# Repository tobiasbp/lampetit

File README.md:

# Lampetit Conversion
A project to convert the Lampetit lamp by Louis Poulsen to a portable LED lamp.

# Create the Gerber files

The following is the high level view of the process. Read the
[description from JLCPVB](https://jlcpcb.com/help/article/16-How-to-generate-Gerber-and-Drill-files-in-KiCad-6)
for all the details.

1. File -> Fabrication outputs -> Gerbers
2. Press _Plot_ to greate Gerbers
3. Press _Generate Drill Files..._

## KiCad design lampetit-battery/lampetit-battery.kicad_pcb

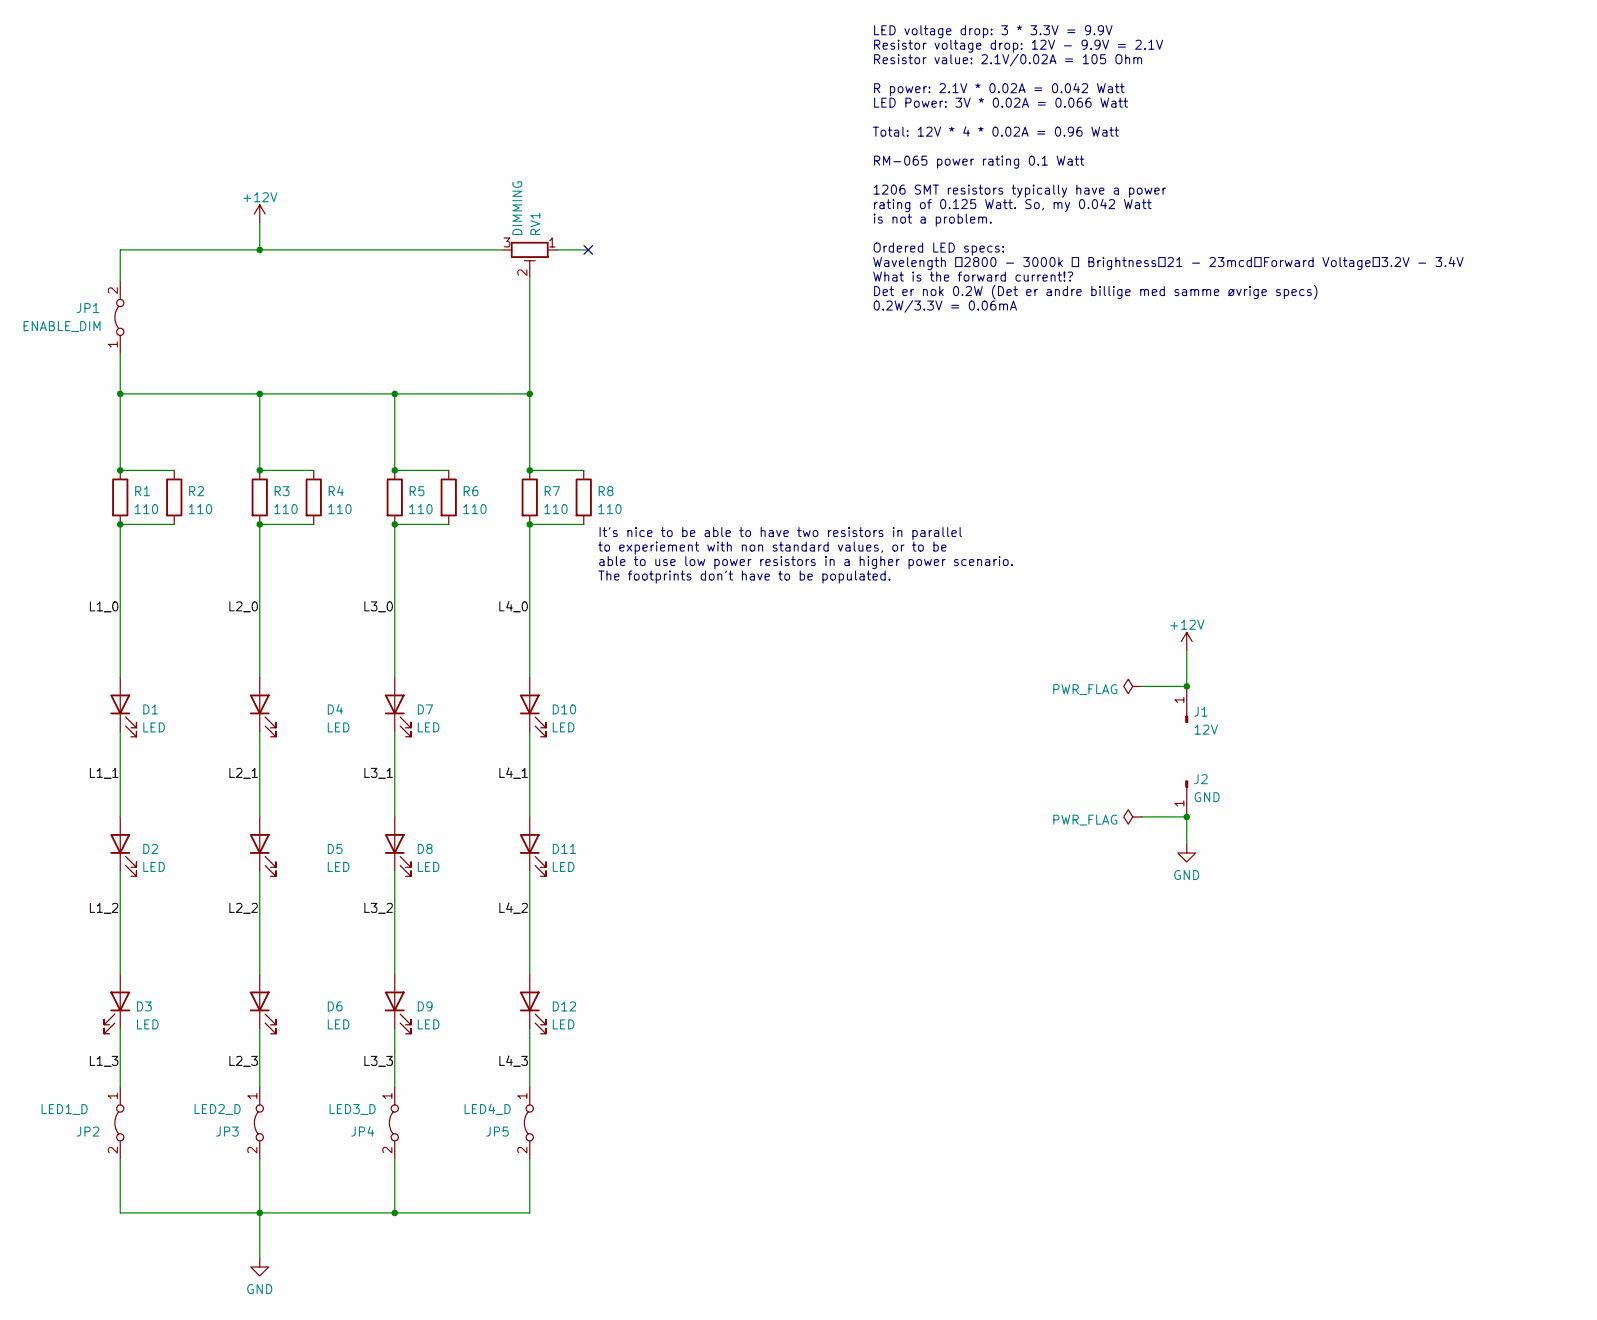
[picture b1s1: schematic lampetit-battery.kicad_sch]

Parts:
D1, D2, D3, D4, D5, D6, D7, D8, D9, D10, D11, D12: LED; LED_PLCC_2835_Handsoldering
J1: 12V; PinHeader_1x01_P2.54mm_Vertical
J2: GND; PinHeader_1x01_P2.54mm_Vertical
JP1: ENABLE_DIM; SolderJumper-2_P1.3mm_Bridged_Pad1.0x1.5mm
JP2: LED1_D; SolderJumper-2_P1.3mm_Bridged_Pad1.0x1.5mm
JP3: LED2_D; SolderJumper-2_P1.3mm_Bridged_Pad1.0x1.5mm
JP4: LED3_D; SolderJumper-2_P1.3mm_Bridged_Pad1.0x1.5mm
JP5: LED4_D; SolderJumper-2_P1.3mm_Bridged_Pad1.0x1.5mm
R1, R2, R3, R4, R5, R6, R7, R8: 110; R_1206_3216Metric_Pad1.30x1.75mm_HandSolder
RV1: DIMMING; Potentiometer_Runtron_RM-065_Vertical

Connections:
+12V: J1.1, JP1.2 (B), RV1.3
/L1_0: D1.2 (A), R1.2, R2.2
/L1_1: D1.1 (K), D2.2 (A)
/L1_2: D2.1 (K), D3.2 (A)
/L1_3: D3.1 (K), JP2.1 (A)
/L2_0: D4.2 (A), R3.2, R4.2
/L2_1: D4.1 (K), D5.2 (A)
/L2_2: D5.1 (K), D6.2 (A)
/L2_3: D6.1 (K), JP3.1 (A)
/L3_0: D7.2 (A), R5.2, R6.2
/L3_1: D7.1 (K), D8.2 (A)
/L3_2: D8.1 (K), D9.2 (A)
/L3_3: D9.1 (K), JP4.1 (A)
/L4_0: D10.2 (A), R7.2, R8.2
/L4_1: D10.1 (K), D11.2 (A)
/L4_2: D11.1 (K), D12.2 (A)
/L4_3: D12.1 (K), JP5.1 (A)
GND: J2.1, JP2.2 (B), JP3.2 (B), JP4.2 (B), JP5.2 (B)
unnamed: JP1.1 (A), R1.1, R2.1, R3.1, R4.1, R5.1, R6.1, R7.1, R8.1, RV1.2

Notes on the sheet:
LED voltage drop: 3 * 3.3V = 9.9V Resistor voltage drop: 12V - 9.9V = 2.1V Resistor value: 2.1V/0.02A = 105 Ohm R power: 2.1V * 0.02A = 0.042 Watt LED Power: 3V * 0.02A = 0.066 Watt Total: 12V * 4 * 0.02A = 0.96 Watt RM-065 power rating 0.1 Watt 1206 SMT resistors typically have a power rating of 0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
It's nice to be able to have two resistors in parallel to experiement with non standard values, or to be able to use low power resistors in a higher power scenario. The footprints don't have to be populated.

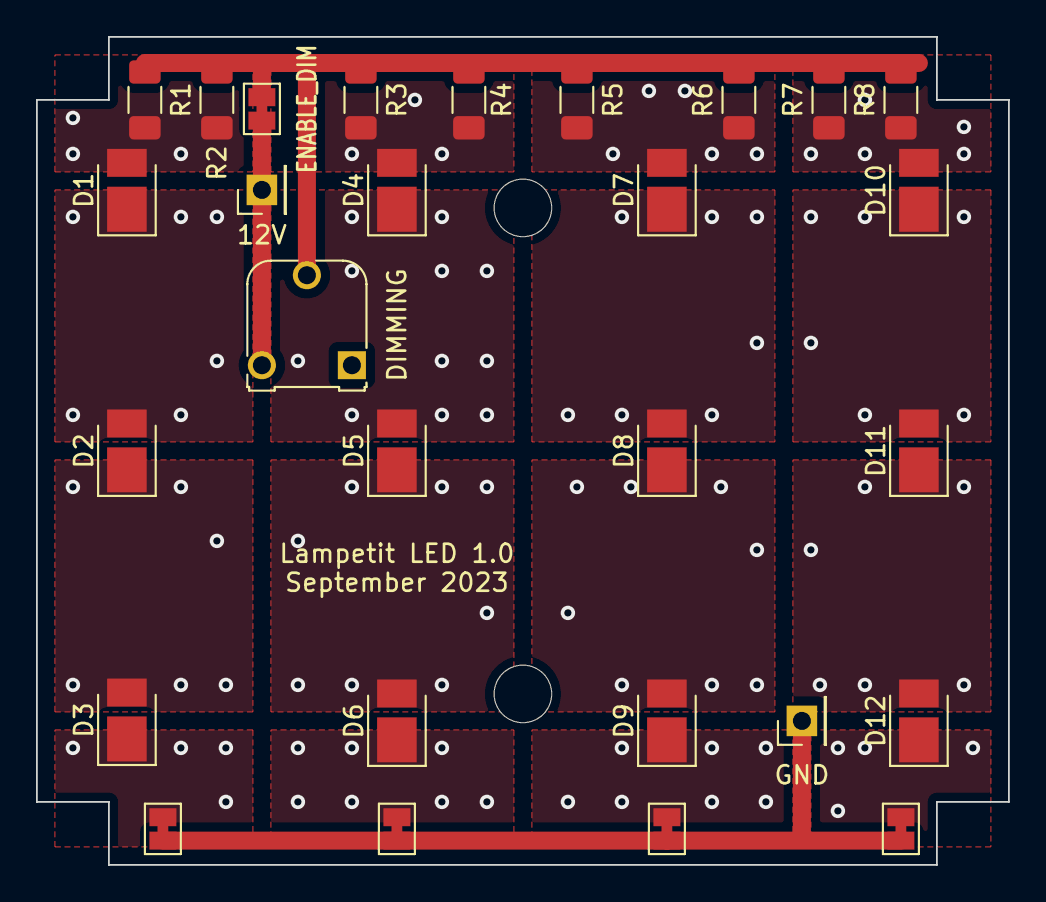
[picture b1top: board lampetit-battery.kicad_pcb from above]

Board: 2 copper layers, 54.0 x 46.0 mm, 28 parts (0 on the bottom side), 19 nets.

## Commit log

2023-09-24 Minor changes to README
2023-09-24 Add KiCad project
2023-09-24 Add gerbers for version v1.0 of the board
